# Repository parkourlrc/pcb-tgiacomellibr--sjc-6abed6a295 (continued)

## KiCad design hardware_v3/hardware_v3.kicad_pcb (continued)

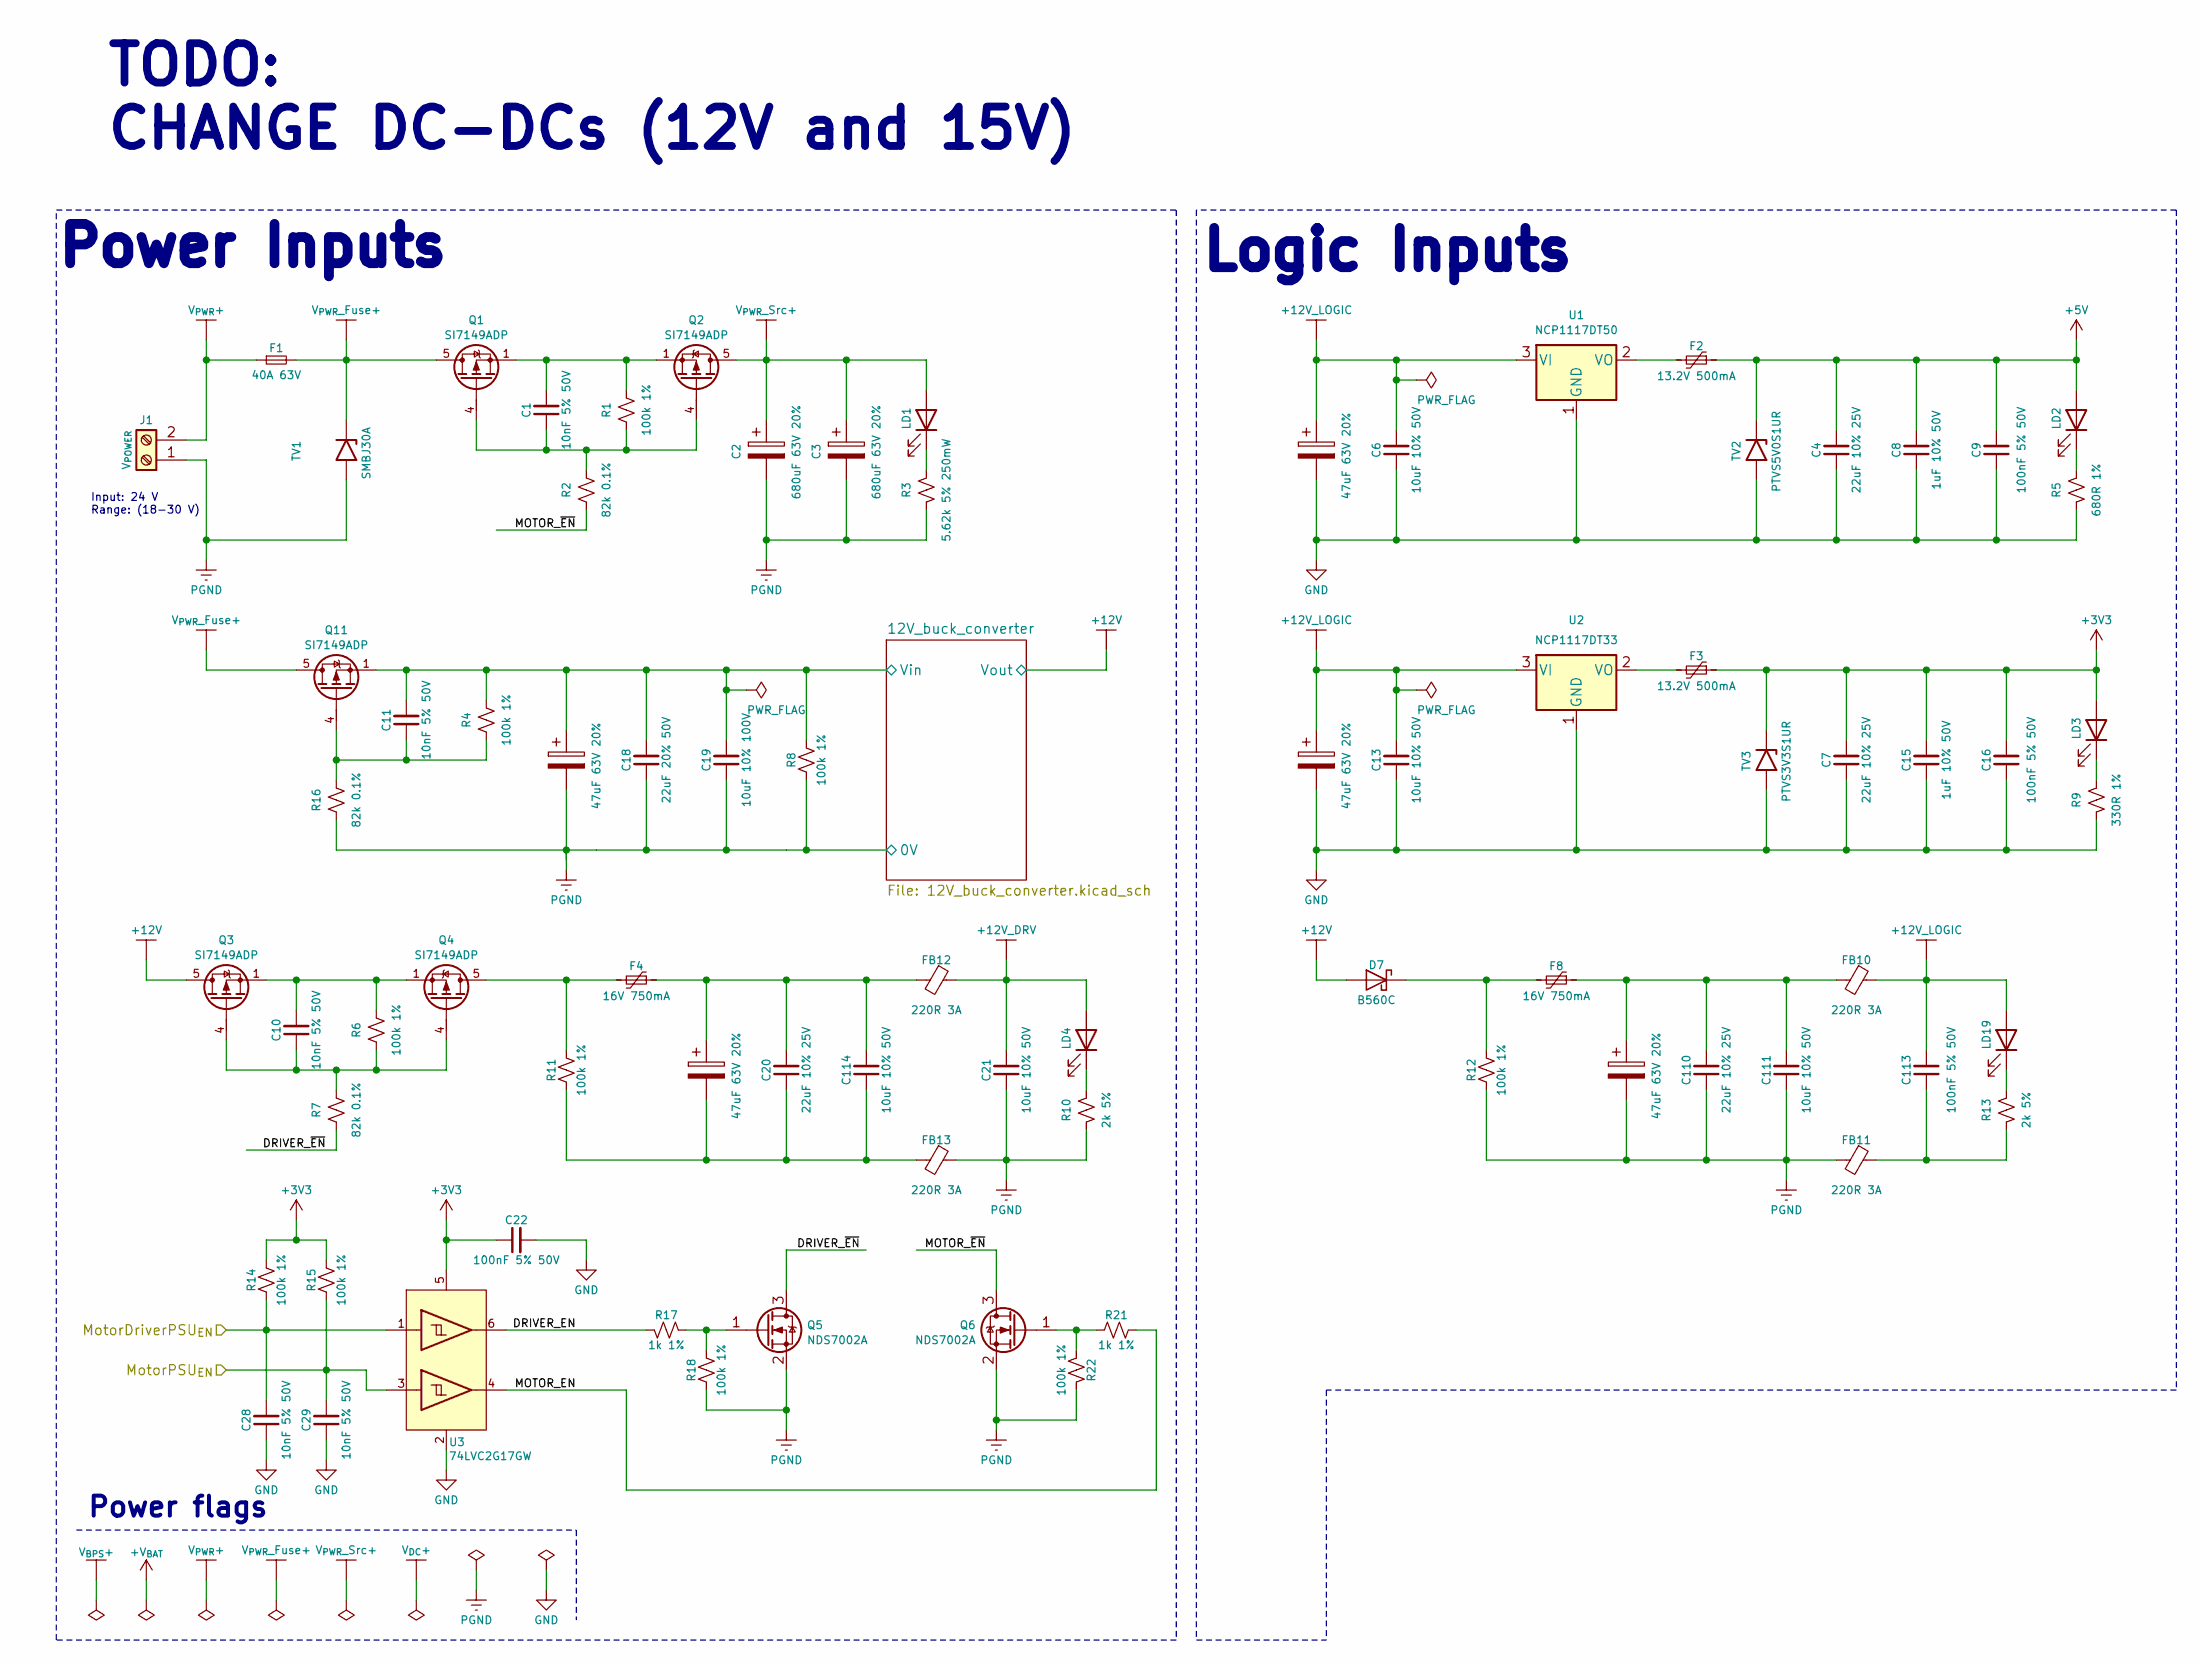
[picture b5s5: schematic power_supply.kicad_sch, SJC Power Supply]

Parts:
C1, C10, C11, C28, C29: 10nF 5% 50V; C_0603_1608Metric; JLCPCB Part # C389113
C2, C3: 680uF 63V 20%; CP_Elec_18x17.5; JLCPCB Part # C249956
C4, C7, C20, C110: 22uF 10% 25V; C_1206_3216Metric; JLCPCB Part # C2178233
C5, C12, C17, C108, C109: 47uF 63V 20%; CP_Elec_8x10.5; JLCPCB Part # C116428
C6, C13, C21, C111, C114: 10uF 10% 50V; C_1206_3216Metric; JLCPCB Part # C13585
C8, C15: 1uF 10% 50V; C_1206_3216Metric; JLCPCB Part # C1848
C9, C16, C22, C113: 100nF 5% 50V; C_0603_1608Metric; JLCPCB Part # C91183
C18: 22uF 20% 50V; C_2220_5750Metric; JLCPCB Part # C2178233
C19: 10uF 10% 100V; C_1210_3225Metric_Pad1.33x2.70mm_HandSolder; JLCPCB Part # C576517
D7: B560C; D_SMC_Handsoldering; JLCPCB Part # C85100
F1: 40A 63V; Fuse_2410_6125Metric_CB61F; JLCPCB Part # C3166275
F2, F3: 13.2V 500mA; Fuse_1206_3216Metric; JLCPCB Part # C75464
F4, F8: 16V 750mA; Fuse_1206_3216Metric; JLCPCB Part # C371166
FB10, FB11, FB12, FB13: 220R 3A; L_0805_2012Metric_Pad1.05x1.20mm_HandSolder; JLCPCB Part # C76818
J1: V_{POWER}; AMASS_XT60PW-F_1x02_P7.20mm_Horizontal; JLCPCB Part # C428722
LD1, LD2, LD3, LD4, LD19: 1.8V @ 5mA; LED_0603_1608Metric_Pad1.05x0.95mm_HandSolder; JLCPCB Part # C165982
Q1, Q2, Q3, Q4, Q11: SI7149ADP; PowerPAK_SO-8_Single; JLCPCB Part # C554002
Q5, Q6: NDS7002A; SOT-23; JLCPCB Part # C74715
R1, R4, R6, R8, R11, R12, R14, R15, R18, R22: 100k 1%; R_0603_1608Metric; JLCPCB Part # C14675
R2, R7, R16: 82k 0.1%; R_0603_1608Metric; JLCPCB Part # C728598
R3: 5.62k 5% 250mW; R_0805_2012Metric_Pad1.20x1.40mm_HandSolder; JLCPCB Part # C425493
R5: 680R 1%; R_0603_1608Metric; JLCPCB Part # C966615
R9: 330R 1%; R_0603_1608Metric; JLCPCB Part # C144102
R10, R13: 2k 5%; R_0603_1608Metric; JLCPCB Part # C103396
R17, R21: 1k 1%; R_0603_1608Metric; JLCPCB Part # C22548
TV1: SMBJ30A; D_SMB_Handsoldering; JLCPCB Part # C83851
TV2: PTVS5V0S1UR; D_SOD-123; JLCPCB Part # C478011
TV3: PTVS3V3S1UR; D_SOD-123; JLCPCB Part # C183521
U1: NCP1117DT50; TO-252-2; JLCPCB Part # C152470
U2: NCP1117DT33; TO-252-2; JLCPCB Part # C88234
U3: 74LVC2G17GW; SOT-363_SC-70-6; JLCPCB Part # C80500

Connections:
+3V3: C7.2, C15.2, C16.2, C22.1, F3.1, LD3.2 (A), R14.2, R15.2, TV3.1 (K), U3.5 (VCC); also elsewhere on the board
+5V: C4.2, C8.2, C9.2, F2.1, LD2.2 (A), TV2.1 (K); also elsewhere on the board
+12V: D7.2 (A), Q3.5 (D); also elsewhere on the board
+12V_DRV: C21.2, FB12.1, LD4.2 (A)
+12V_LOGIC: C5.1, C6.2, C12.1, C13.2, C113.2, FB10.1, LD19.2 (A), U1.3 (VI), U2.3 (VI)
/Power Supply/12V_buck_converter/Vin: C11.2, C17.1, C18.2, C19.2, Q11.1 (S), Q11.2 (S), Q11.3 (S), R4.2, R8.2; also elsewhere on the board
/Power Supply/DRIVER_EN: R17.2, U3.6 (1Y)
/Power Supply/DRIVER_~EN: Q5.3 (D), R7.1
/Power Supply/MOTOR_EN: R21.2, U3.4 (2Y)
/Power Supply/MOTOR_~EN: Q6.3 (D), R2.1
/Power Supply/MotorDriverPSU_{EN}: C28.2, R14.1, U3.1 (1A)
/Power Supply/MotorPSU_{EN}: C29.2, R15.1, U3.3 (2A)
GND: C4.1, C5.2, C6.1, C7.1, C8.1, C9.1, C12.2, C13.1, C15.1, C16.1, C22.2, C28.1, C29.1, R5.2, R9.2, TV2.2 (A), TV3.2 (A), U1.1 (GND), U2.1 (GND), U3.2 (GND); also elsewhere on the board
unnamed: C1.2, Q1.1 (S), Q1.2 (S), Q1.3 (S), Q2.1 (S), Q2.2 (S), Q2.3 (S), R1.2
unnamed: C10.2, Q3.1 (S), Q3.2 (S), Q3.3 (S), Q4.1 (S), Q4.2 (S), Q4.3 (S), R6.2
unnamed: C20.2, C108.1, C114.2, F4.1, FB12.2
unnamed: C20.1, C108.2, C114.1, FB13.2, R11.1
unnamed: C109.1, C110.2, C111.2, F8.1, FB10.2
unnamed: C113.1, FB11.1, R13.2
unnamed: D7.1 (K), F8.2, R12.2
unnamed: LD1.1 (K), R3.1
unnamed: LD2.1 (K), R5.1
unnamed: LD3.1 (K), R9.1
unnamed: LD4.1 (K), R10.1
unnamed: LD19.1 (K), R13.1
unnamed: C1.1, Q1.4 (G), Q2.4 (G), R1.1, R2.2
unnamed: C10.1, Q3.4 (G), Q4.4 (G), R6.1, R7.2
unnamed: F4.2, Q4.5 (D), R11.2
unnamed: Q5.1 (G), R17.1, R18.2
unnamed: Q6.1 (G), R21.1, R22.2
unnamed: C11.1, Q11.4 (G), R4.1, R16.2
unnamed: F2.2, U1.2 (VO)
unnamed: F3.2, U2.2 (VO)
PGND: C2.2, C3.2, C17.2, C18.1, C19.1, C21.1, C109.2, C110.1, C111.1, FB11.2, FB13.1, J1.1, Q5.2 (S), Q6.2 (S), R3.2, R8.1, R10.2, R12.1, R16.1, R18.1, R22.1, TV1.2 (A); also elsewhere on the board
V_{PWR}+: F1.1, J1.2
V_{PWR}_Fuse+: F1.2, Q1.5 (D), Q11.5 (D), TV1.1 (K)
V_{PWR}_Src+: C2.1, C3.1, LD1.2 (A), Q2.5 (D); also elsewhere on the board

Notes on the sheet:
TODO: CHANGE DC-DCs (12V and 15V)
Power flags
Logic Inputs
Input: 24 V Range: (18-30 V)
Power Inputs

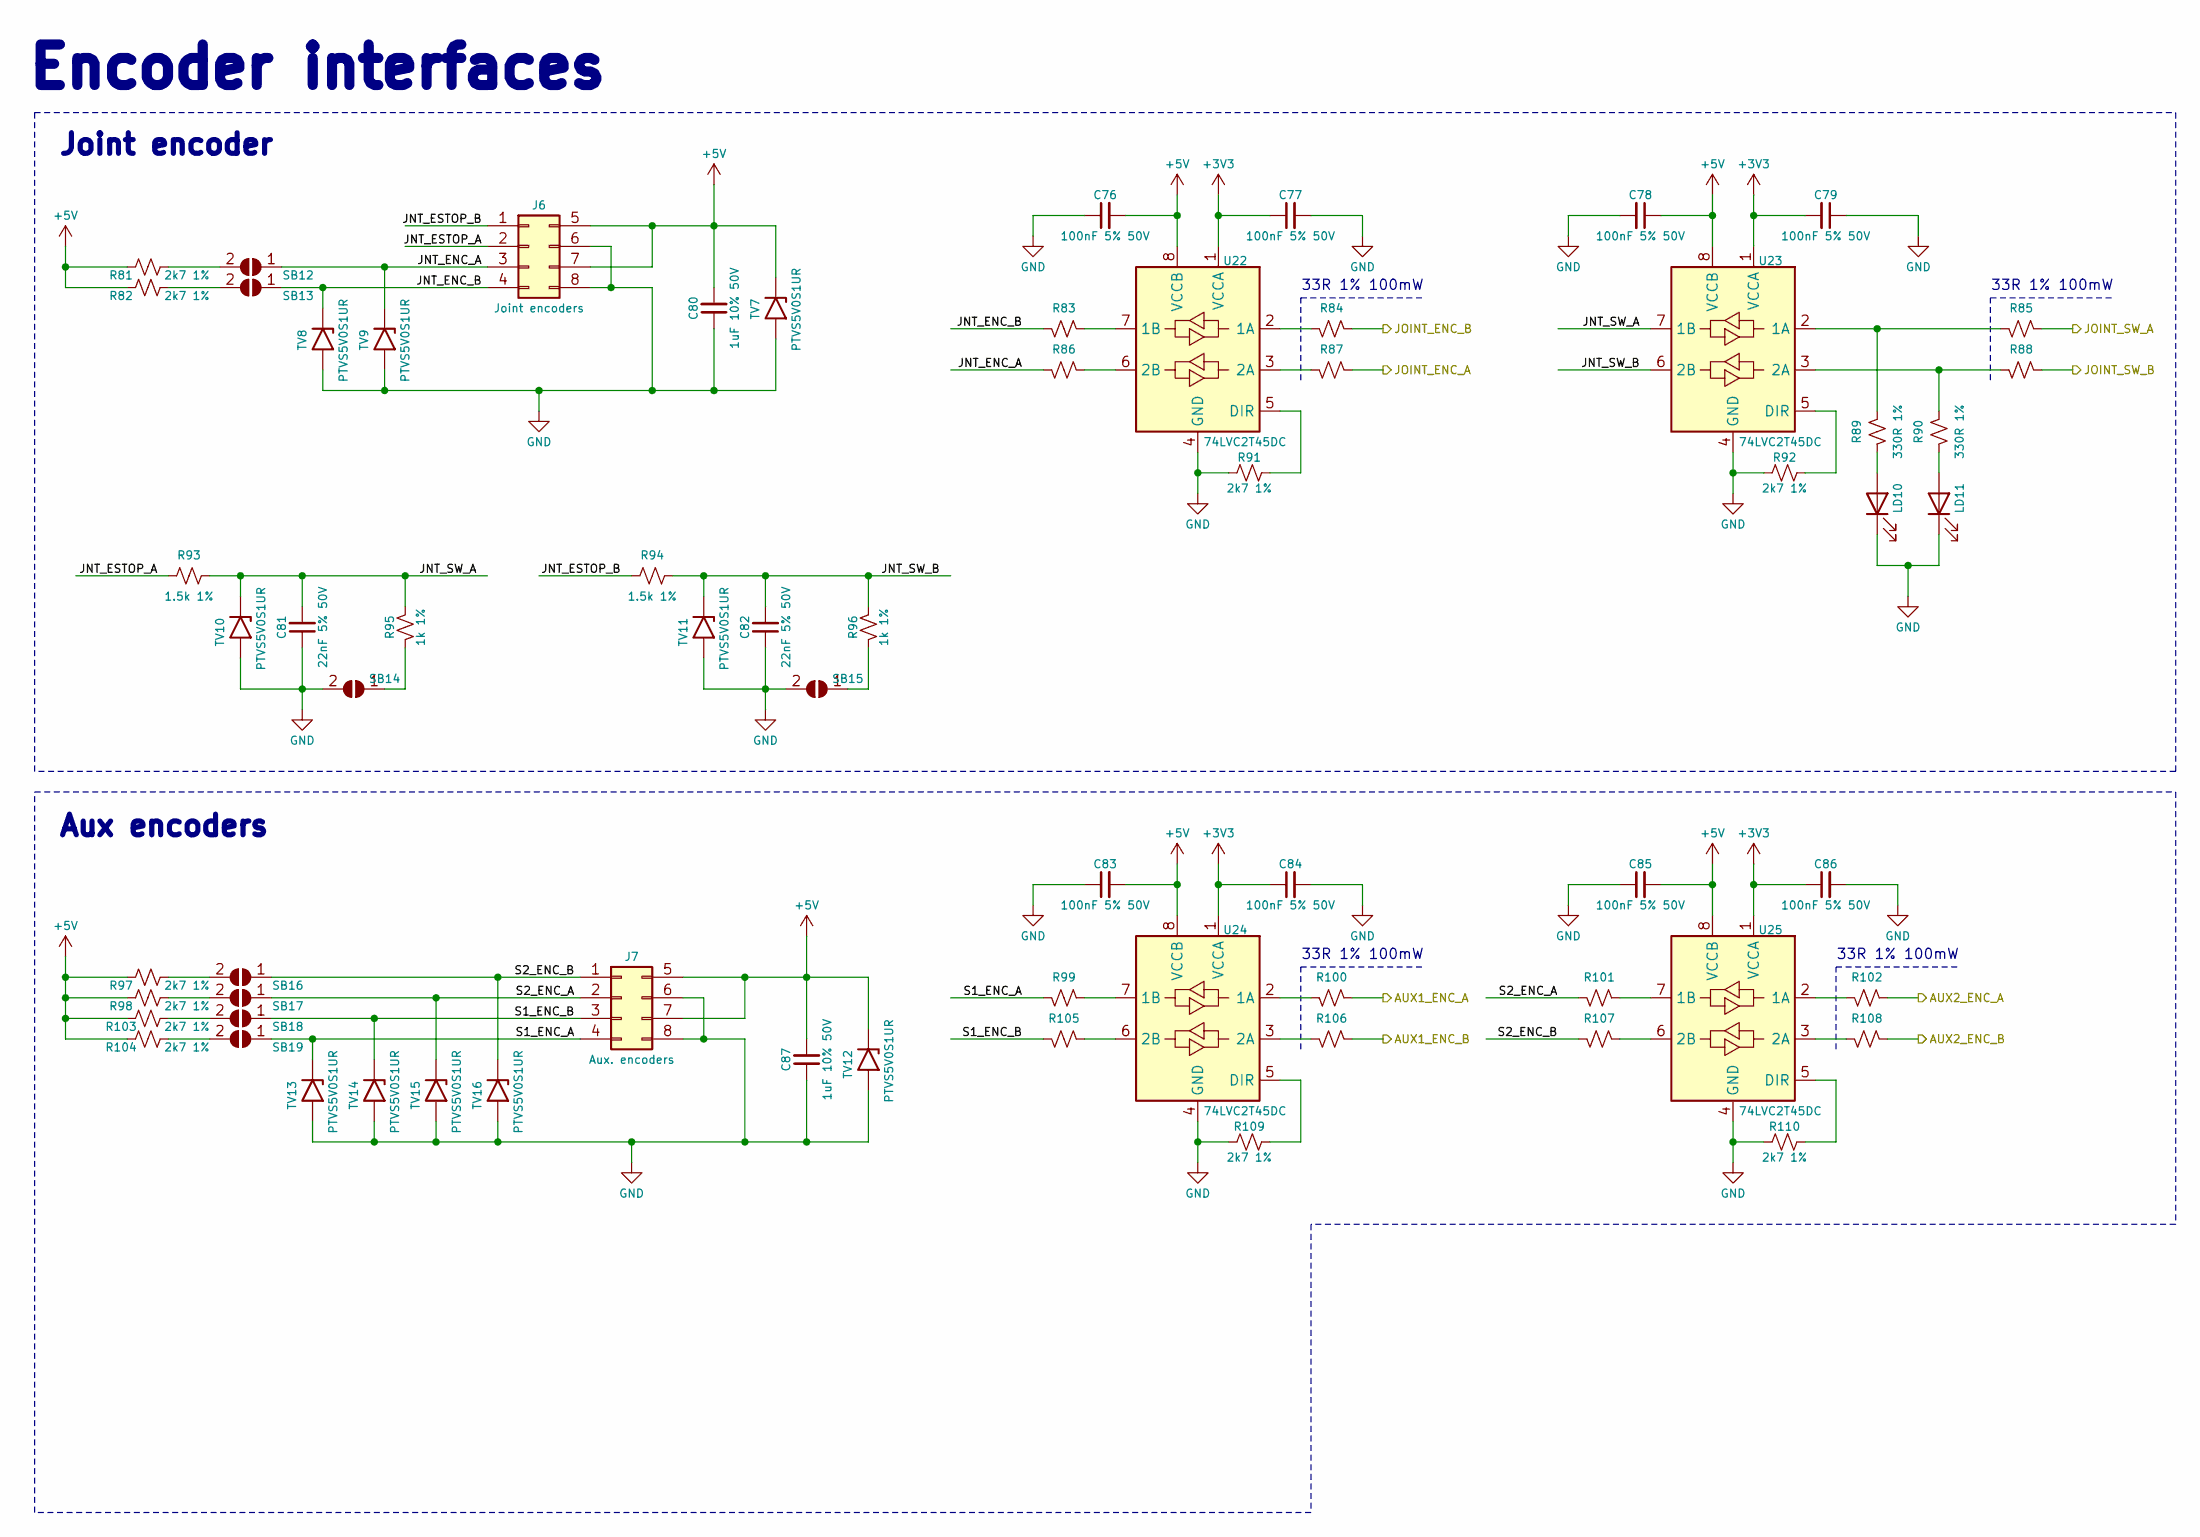
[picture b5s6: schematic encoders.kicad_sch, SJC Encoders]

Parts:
C76, C77, C78, C79, C83, C84, C85, C86: 100nF 5% 50V; C_0603_1608Metric; JLCPCB Part # C91183
C80, C87: 1uF 10% 50V; C_1206_3216Metric; JLCPCB Part # C1848
C81, C82: 22nF 5% 50V; C_0603_1608Metric; JLCPCB Part # C277528
J6: Joint encoders; Molex_Micro-Fit_3.0_43045-0812_2x04_P3.00mm_Vertical
J7: Aux. encoders; Molex_Micro-Fit_3.0_43045-0812_2x04_P3.00mm_Vertical
LD10, LD11: 1.8V @ 5mA; LED_0603_1608Metric_Pad1.05x0.95mm_HandSolder; JLCPCB Part # C165982
R81, R82, R91, R92, R97, R98, R103, R104, R109, R110: 2k7 1%; R_0603_1608Metric; JLCPCB Part # C114612
R83, R84, R85, R86, R87, R88, R99, R100, R101, R102, R105, R106, R107, R108: 33R 1%; R_0603_1608Metric; JLCPCB Part # C108661
R89, R90: 330R 1%; R_0603_1608Metric; JLCPCB Part # C144102
R93, R94: 1.5k 1%; R_0603_1608Metric; JLCPCB Part # C285210
R95, R96: 1k 1%; R_0603_1608Metric; JLCPCB Part # C22548
SB12, SB13, SB14, SB15, SB16, SB17, SB18, SB19: SolderJumper-2_P1.3mm_Open_RoundedPad1.0x1.5mm
TV7, TV8, TV9, TV10, TV11, TV12, TV13, TV14, TV15, TV16: PTVS5V0S1UR; D_SOD-123; JLCPCB Part # C478011
U22, U23, U24, U25: 74LVC2T45DC; VSSOP-8_2.3x2mm_P0.5mm; JLCPCB Part # C730237

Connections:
+3V3: C77.1, C79.2, C84.1, C86.1, U22.1 (VCCA), U23.1 (VCCA), U24.1 (VCCA), U25.1 (VCCA); also elsewhere on the board
+5V: C76.2, C78.1, C80.2, C83.2, C85.2, C87.2, J6.5, J6.7, J7.5, J7.7, R81.2, R82.2, R97.1, R98.1, R103.1, R104.1, TV7.1 (K), TV12.1 (K), U22.8 (VCCB), U23.8 (VCCB), U24.8 (VCCB), U25.8 (VCCB); also elsewhere on the board
/Control/AUX1_ENC_CH1: R100.1; also elsewhere on the board
/Control/AUX1_ENC_CH2: R106.1; also elsewhere on the board
/Control/AUX2_ENC_CH1: R102.1; also elsewhere on the board
/Control/AUX2_ENC_CH2: R108.1; also elsewhere on the board
/Control/JOINT_ENC_CH1: R87.1; also elsewhere on the board
/Control/JOINT_ENC_CH2: R84.1; also elsewhere on the board
/Control/JOINT_SW_L: R85.1; also elsewhere on the board
/Control/JOINT_SW_R: R88.1; also elsewhere on the board
/Encoders/JNT_ENC_A: J6.3, R86.2, SB12.1 (A), TV9.1 (K)
/Encoders/JNT_ENC_B: J6.4, R83.2, SB13.1 (A), TV8.1 (K)
/Encoders/JNT_ESTOP_A: J6.2, R93.1
/Encoders/JNT_ESTOP_B: J6.1, R94.1
/Encoders/JNT_SW_A: C81.2, R93.2, R95.1, TV10.1 (K), U23.7 (1B)
/Encoders/JNT_SW_B: C82.2, R94.2, R96.1, TV11.1 (K), U23.6 (2B)
/Encoders/S1_ENC_A: J7.4, R99.2, SB19.1 (A), TV13.1 (K)
/Encoders/S1_ENC_B: J7.3, R105.2, SB18.1 (A), TV14.1 (K)
/Encoders/S2_ENC_A: J7.2, R101.2, SB17.1 (A), TV15.1 (K)
/Encoders/S2_ENC_B: J7.1, R107.2, SB16.1 (A), TV16.1 (K)
GND: C76.1, C77.2, C78.2, C79.1, C80.1, C81.1, C82.1, C83.1, C84.2, C85.1, C86.2, C87.1, J6.6, J6.8, J7.6, J7.8, LD10.1 (K), LD11.1 (K), R91.1, R92.1, R109.1, R110.1, SB14.2 (B), SB15.2 (B), TV7.2 (A), TV8.2 (A), TV9.2 (A), TV10.2 (A), TV11.2 (A), TV12.2 (A), TV13.2 (A), TV14.2 (A), TV15.2 (A), TV16.2 (A), U22.4 (GND), U23.4 (GND), U24.4 (GND), U25.4 (GND); also elsewhere on the board
unnamed: LD10.2 (A), R89.2
unnamed: LD11.2 (A), R90.2
unnamed: R81.1, SB12.2 (B)
unnamed: R82.1, SB13.2 (B)
unnamed: R95.2, SB14.1 (A)
unnamed: R96.2, SB15.1 (A)
unnamed: R97.2, SB16.2 (B)
unnamed: R98.2, SB17.2 (B)
unnamed: R103.2, SB18.2 (B)
unnamed: R104.2, SB19.2 (B)
unnamed: R84.2, U22.2 (1A)
unnamed: R83.1, U22.7 (1B)
unnamed: R87.2, U22.3 (2A)
unnamed: R86.1, U22.6 (2B)
unnamed: R91.2, U22.5 (DIR)
unnamed: R85.2, R89.1, U23.2 (1A)
unnamed: R88.2, R90.1, U23.3 (2A)
unnamed: R92.2, U23.5 (DIR)
unnamed: R100.2, U24.2 (1A)
unnamed: R99.1, U24.7 (1B)
unnamed: R106.2, U24.3 (2A)
unnamed: R105.1, U24.6 (2B)
unnamed: R109.2, U24.5 (DIR)
unnamed: R102.2, U25.2 (1A)
unnamed: R101.1, U25.7 (1B)
unnamed: R108.2, U25.3 (2A)
unnamed: R107.1, U25.6 (2B)
unnamed: R110.2, U25.5 (DIR)

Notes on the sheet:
33R 1% 100mW
Joint encoder
Aux encoders
Encoder interfaces

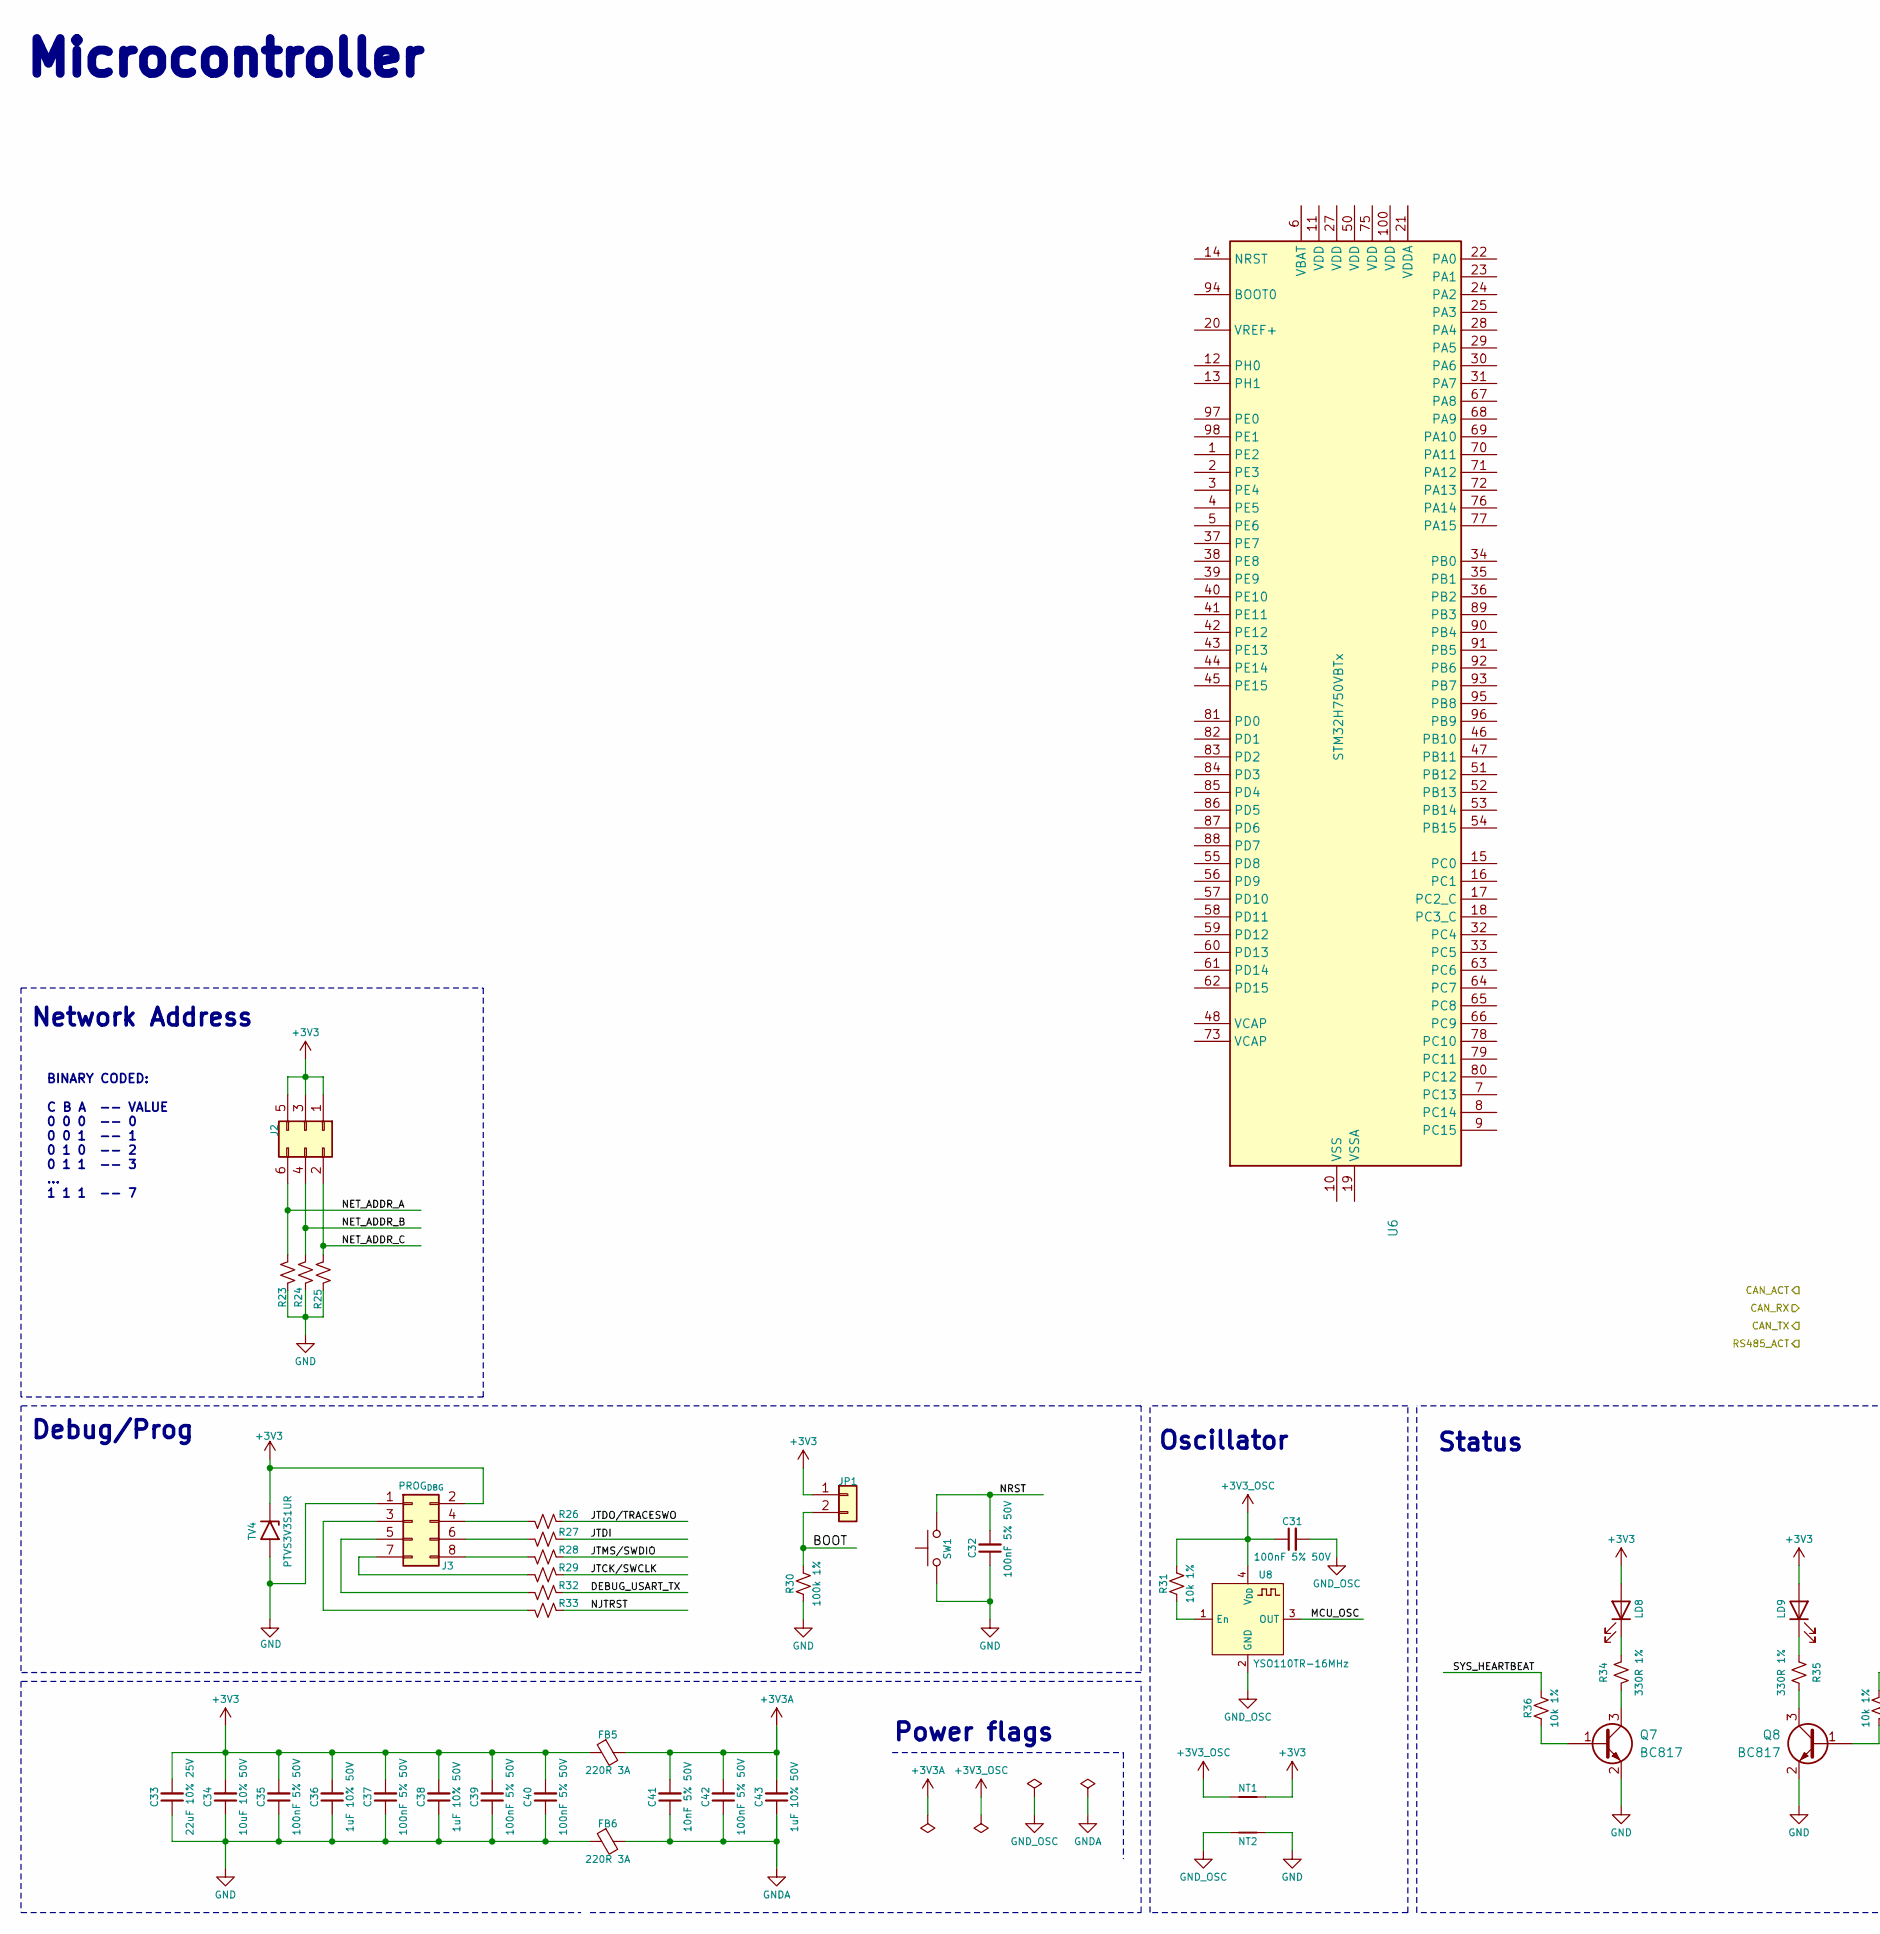
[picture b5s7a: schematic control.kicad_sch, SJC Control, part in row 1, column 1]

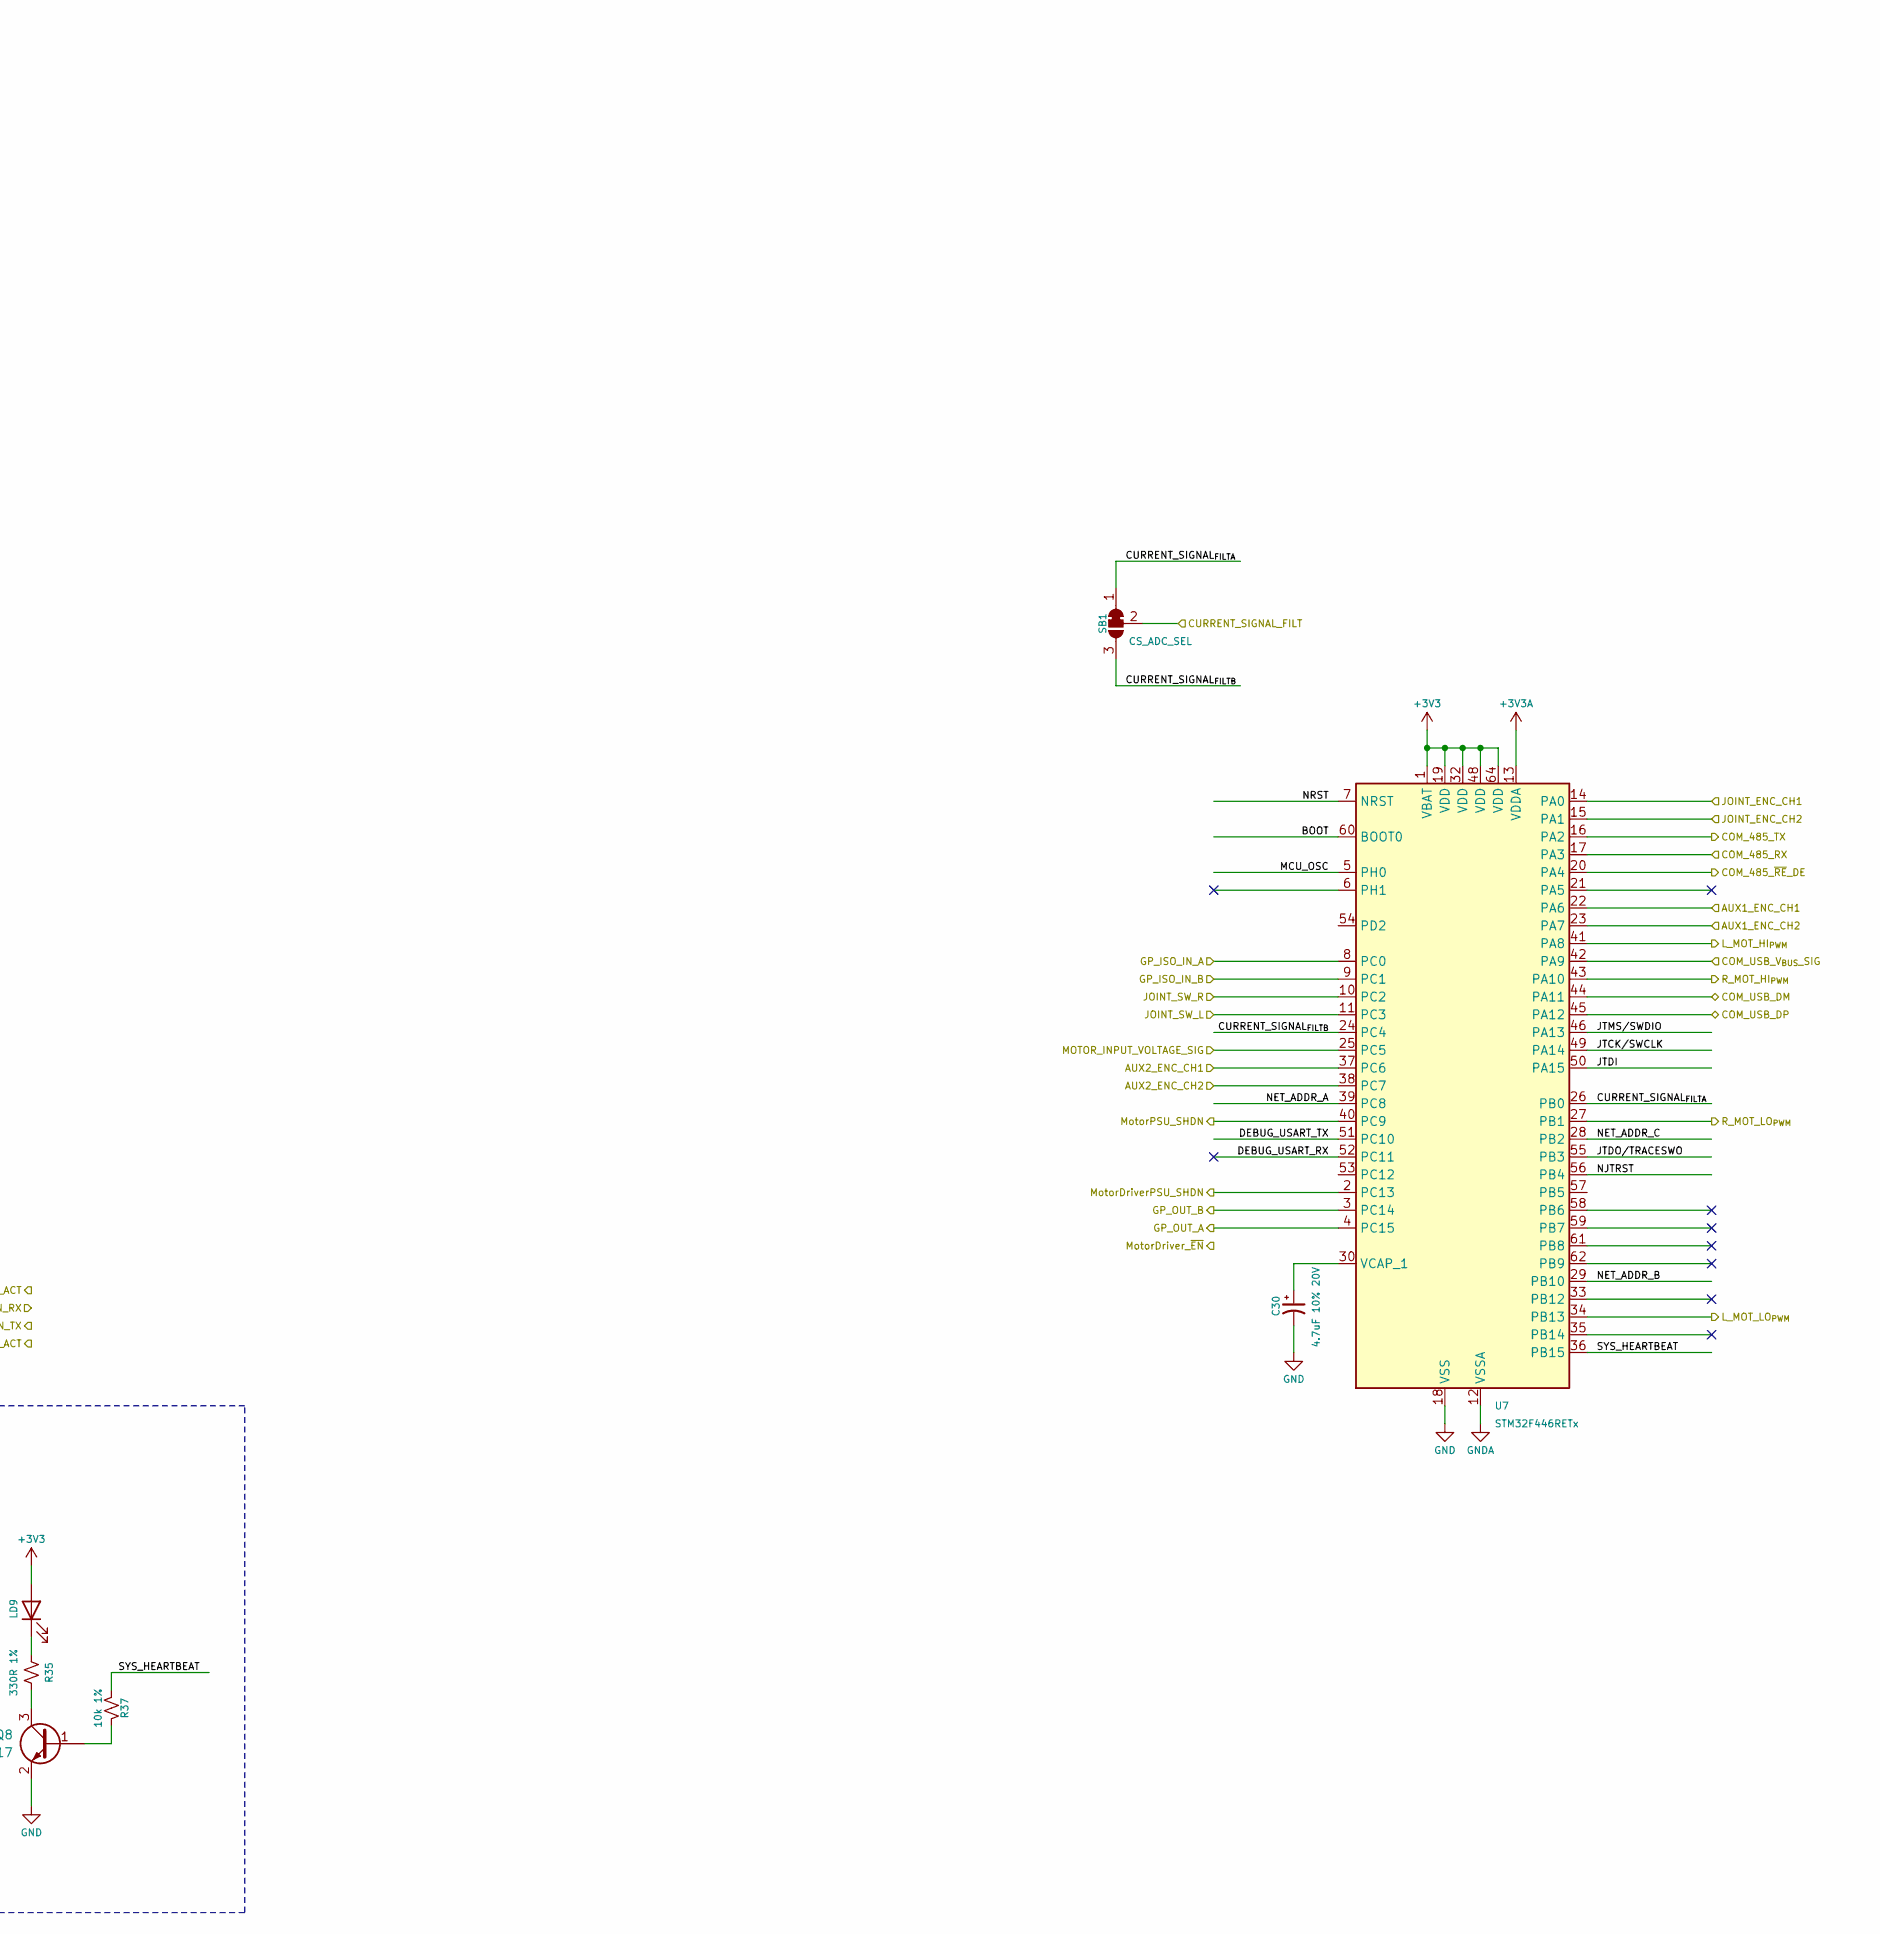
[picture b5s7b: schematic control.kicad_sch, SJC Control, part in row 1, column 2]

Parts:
C30: 4.7uF 10% 20V; CP_EIA-3528-15_AVX-H_Pad1.50x2.35mm_HandSolder; JLCPCB Part # C308921
C31, C32, C35, C37, C39, C40, C42: 100nF 5% 50V; C_0603_1608Metric; JLCPCB Part # C91183
C33: 22uF 10% 25V; C_1206_3216Metric; JLCPCB Part # C2178233
C34: 10uF 10% 50V; C_1206_3216Metric; JLCPCB Part # C13585
C36, C38, C43: 1uF 10% 50V; C_1206_3216Metric; JLCPCB Part # C1848
C41: 10nF 5% 50V; C_0603_1608Metric; JLCPCB Part # C389113
FB5, FB6: 220R 3A; L_0805_2012Metric_Pad1.05x1.20mm_HandSolder; JLCPCB Part # C76818
J2: NET ADDRESS; PinHeader_2x03_P2.54mm_Vertical; JLCPCB Part # C225518
J3: PROG_{DBG}; PinHeader_2x04_P2.54mm_Vertical; JLCPCB Part # C225519
JP1: Boot; PinHeader_1x02_P2.54mm_Vertical; JLCPCB Part # C225477
LD8, LD9: 1.8V @ 5mA; LED_0603_1608Metric_Pad1.05x0.95mm_HandSolder; JLCPCB Part # C165982
NT1, NT2: NetTie-2_SMD_Pad0.5mm
Q7, Q8: BC817; SOT-23; JLCPCB Part # C52801
R23, R24, R25, R31, R36, R37: 10k 1%; R_0603_1608Metric; JLCPCB Part # C98220
R26, R27, R28, R29, R32, R33: 33R 1%; R_0603_1608Metric; JLCPCB Part # C108661
R30: 100k 1%; R_0603_1608Metric; JLCPCB Part # C14675
R34, R35: 330R 1%; R_0603_1608Metric; JLCPCB Part # C144102
SB1: CS_ADC_SEL; SolderJumper-3_P1.3mm_Bridged2Bar12_RoundedPad1.0x1.5mm
SW1: Tactile Switch; SW_Tactile_SPST_NO_Straight_CK_PTS636Sx25SMTRLFS; JLCPCB Part # C2689642
TV4: PTVS3V3S1UR; D_SOD-123; JLCPCB Part # C183521
U6: STM32H750VBTx; LQFP-100_14x14mm_P0.5mm; JLCPCB Part # C404010
U7: STM32F446RETx; LQFP-64_10x10mm_P0.5mm; JLCPCB Part # C69336
U8: YSO110TR-16MHz; Oscillator_SMD_YXC_YSO110TR_7050-4Pin_7.0x5.0mm; JLCPCB Part # C669093

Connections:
+3V3: C33.2, C34.2, C35.2, C36.2, C37.2, C38.2, C39.2, C40.2, FB5.1, J2.1, J2.3, J2.5, J3.2, JP1.1, LD8.2 (A), LD9.2 (A), NT1.1, TV4.1 (K), U7.1 (VBAT), U7.19 (VDD), U7.32 (VDD), U7.48 (VDD), U7.64 (VDD); also elsewhere on the board
+3V3A: C41.2, C42.2, C43.2, FB5.2, U7.13 (VDDA)
+3V3_OSC: C31.1, NT1.2, R31.2, U8.4 (V_{DD})
/Control/AUX1_ENC_CH1: U7.22 (PA6); also elsewhere on the board
/Control/AUX1_ENC_CH2: U7.23 (PA7); also elsewhere on the board
/Control/AUX2_ENC_CH1: U7.37 (PC6); also elsewhere on the board
/Control/AUX2_ENC_CH2: U7.38 (PC7); also elsewhere on the board
/Control/BOOT: JP1.2, R30.2, U7.60 (BOOT0)
/Control/COM_485_RX: U7.17 (PA3); also elsewhere on the board
/Control/COM_485_TX: U7.16 (PA2); also elsewhere on the board
/Control/COM_485_~RE_DE: U7.20 (PA4); also elsewhere on the board
/Control/COM_USB_DM: U7.44 (PA11)
/Control/COM_USB_DP: U7.45 (PA12)
/Control/COM_USB_V_{BUS}_SIG: U7.42 (PA9)
/Control/CURRENT_SIGNAL_FILT: SB1.2 (C); also elsewhere on the board
/Control/CURRENT_SIGNAL_{FILTA}: SB1.1 (A), U7.26 (PB0)
/Control/CURRENT_SIGNAL_{FILTB}: SB1.3 (B), U7.24 (PC4)
/Control/DEBUG_USART_RX: U7.52 (PC11)
/Control/DEBUG_USART_TX: R32.1, U7.51 (PC10)
/Control/GP_ISO_IN_A: U7.8 (PC0); also elsewhere on the board
/Control/GP_ISO_IN_B: U7.9 (PC1); also elsewhere on the board
/Control/GP_OUT_A: U7.4 (PC15); also elsewhere on the board
/Control/GP_OUT_B: U7.3 (PC14); also elsewhere on the board
/Control/JOINT_ENC_CH1: U7.14 (PA0); also elsewhere on the board
/Control/JOINT_ENC_CH2: U7.15 (PA1); also elsewhere on the board
/Control/JOINT_SW_L: U7.11 (PC3); also elsewhere on the board
/Control/JOINT_SW_R: U7.10 (PC2); also elsewhere on the board
/Control/JTCK/SWCLK: R29.1, U7.49 (PA14)
/Control/JTDI: R27.1, U7.50 (PA15)
/Control/JTDO/TRACESWO: R26.1, U7.55 (PB3)
/Control/JTMS/SWDIO: R28.1, U7.46 (PA13)
/Control/L_MOT_HI_{PWM}: U7.41 (PA8); also elsewhere on the board
/Control/L_MOT_LO_{PWM}: U7.34 (PB13); also elsewhere on the board
/Control/MCU_OSC: U7.5 (PH0), U8.3 (OUT)
/Control/MotorDriverPSU_SHDN: U7.2 (PC13)
/Control/MotorPSU_SHDN: U7.40 (PC9)
/Control/NET_ADDR_A: J2.6, R23.1, U7.39 (PC8)
/Control/NET_ADDR_B: J2.4, R24.1, U7.29 (PB10)
/Control/NET_ADDR_C: J2.2, R25.1, U7.28 (PB2)
/Control/NJTRST: R33.1, U7.56 (PB4)
/Control/NRST: C32.2, SW1.2, U7.7 (NRST)
/Control/R_MOT_HI_{PWM}: U7.43 (PA10); also elsewhere on the board
/Control/R_MOT_LO_{PWM}: U7.27 (PB1)
/Control/SYS_HEARTBEAT: R36.2, R37.2, U7.36 (PB15)
/Motor/VS_{SRC}: U7.25 (PC5); also elsewhere on the board
GND: C30.2, C32.1, C33.1, C34.1, C35.1, C36.1, C37.1, C38.1, C39.1, C40.1, FB6.1, J3.1, NT2.2, Q7.2 (E), Q8.2 (E), R23.2, R24.2, R25.2, R30.1, SW1.1, TV4.2 (A), U7.18 (VSS), U7.31 (VSS), U7.47 (VSS), U7.63 (VSS); also elsewhere on the board
GNDA: C41.1, C42.1, C43.1, FB6.2, U7.12 (VSSA)
GND_OSC: C31.2, NT2.1, U8.2 (GND)
unnamed: J3.3, R33.2
unnamed: J3.4, R26.2
unnamed: J3.5, R32.2
unnamed: J3.6, R27.2
unnamed: J3.7, R29.2
unnamed: J3.8, R28.2
unnamed: LD8.1 (K), R34.1
unnamed: LD9.1 (K), R35.1
unnamed: Q7.1 (B), R36.1
unnamed: Q7.3 (C), R34.2
unnamed: Q8.1 (B), R37.1
unnamed: Q8.3 (C), R35.2
unnamed: U6.10 (VSS), U6.26 (VSS), U6.49 (VSS), U6.74 (VSS), U6.99 (VSS)
unnamed: C30.1, U7.30 (VCAP_1)
unnamed: R31.1, U8.1 (En)

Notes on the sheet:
Microcontroller
Power flags
Network Address
BINARY CODED: C B A -- VALUE 0 0 0 -- 0 0 0 1 -- 1 0 1 0 -- 2 0 1 1 -- 3 ... 1 1 1 -- 7
Debug/Prog
Status
Oscillator
